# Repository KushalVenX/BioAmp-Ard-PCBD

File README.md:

# Repository Overview

This repository contains a PCB design for the "BioAmp-EXG-Pill" from Upside Down Labs, presented as an open-source hardware project. The design has been adapted and routed on an Arduino template.

## Description

The repository features a PCB design that is a routed adaptation of the BioAmp-EXG-Pill PCB. Although this design utilizes an Arduino template and does not exactly replicate the original design, it serves as a valuable educational resource.

## Purpose:

The repository is intended for educational purposes and learning. It offers an opportunity to:

-**Explore PCB Design**: Understand and study the layout and routing of a real-world PCB.

-**Experiment**: Modify the design for personal projects or educational exercises.

-**Teach**: Use this routed version as a teaching tool for PCB design concepts.

## Original Schematic Credits:

**UPSIDE DOWN LABS**

website: https://upsidedownlabs.tech/

Store: https://store.upsidedownlabs.tech/

github: https://github.com/upsidedownlabs

## Arduino Template credits:

The Arduino template used in this design is based on the Arduino UNO board design by Arduino.cc.

## License:

For details about the licensing of the original design of BioAmp-EXG-Pill, please refer to the Upside Down Labs GitHub repository.

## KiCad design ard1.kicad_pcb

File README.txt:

# Repository Overview
-------------------

This repository contains a PCB design for the "BioAmp-EXG-Pill" from Upside Down Labs, presented as an open-source hardware project. The design has been adapted and routed on an Arduino template.

## Description
------------

The repository features a PCB design that is a routed adaptation of the BioAmp-EXG-Pill PCB. Although this design utilizes an Arduino template and does not exactly replicate the original design, it serves as a valuable educational resource.

## Purpose:
---------
The repository is intended for educational purposes and learning. It offers an opportunity to:

-Explore PCB Design: Understand and study the layout and routing of a real-world PCB.
-Experiment: Modify the design for personal projects or educational exercises.
-Teach: Use this routed version as a teaching tool for PCB design concepts.

## Original Schematic Credits:
---------------------------
website: https://upsidedownlabs.tech/
Store: https://store.upsidedownlabs.tech/
github: https://github.com/upsidedownlabs

## Arduino Template credits:
-------------------------

The Arduino template used in this design is based on the Arduino UNO board design by Arduino.cc.

## License:
--------
For details about the licensing of the original design of BioAmp-EXG-Pill, please refer to the Upside Down Labs GitHub repository.

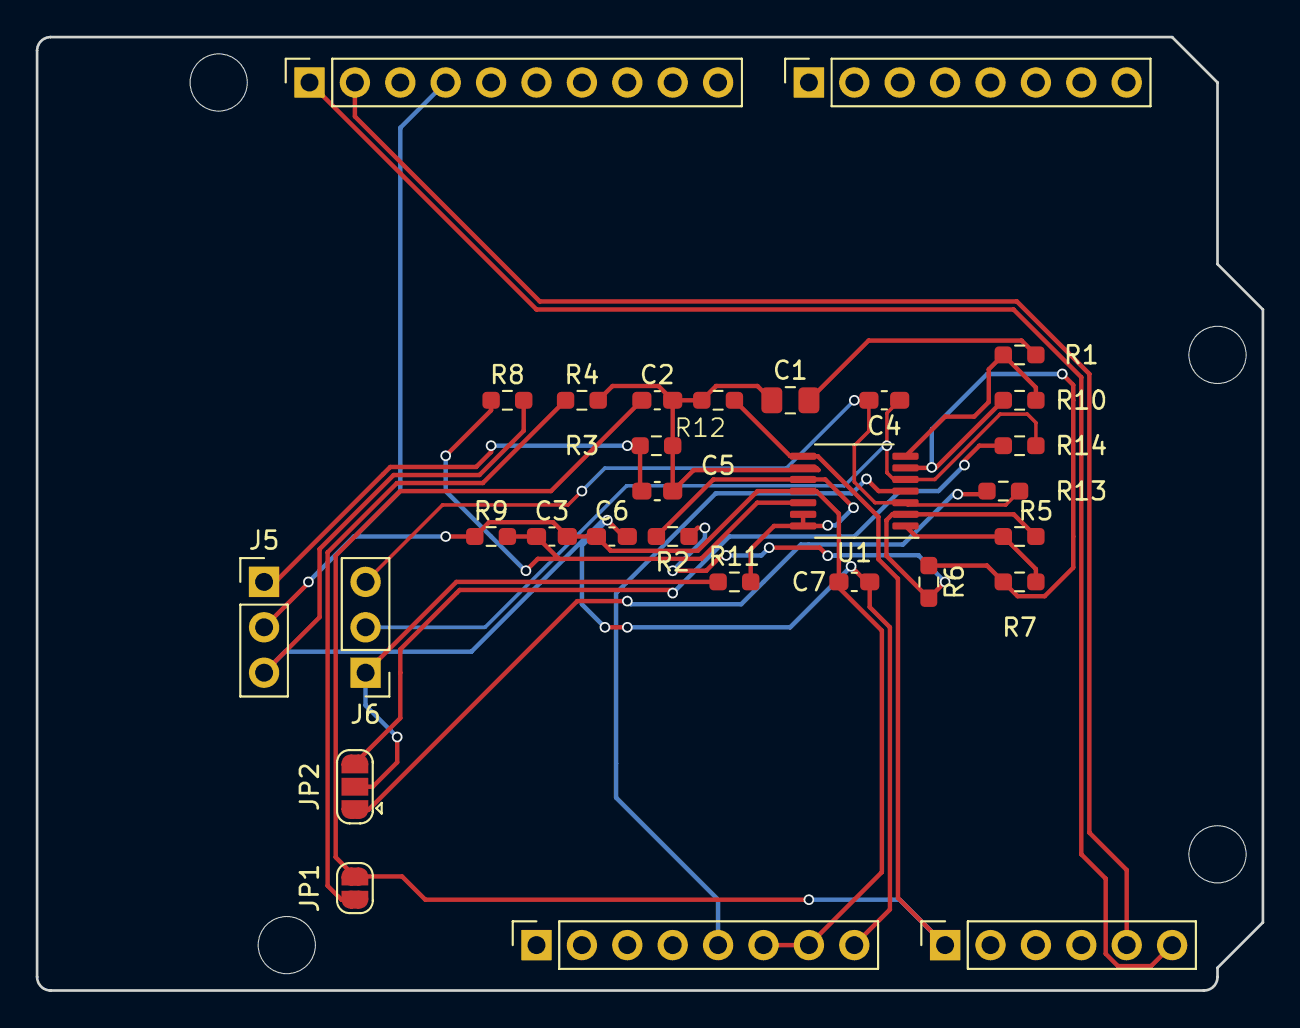
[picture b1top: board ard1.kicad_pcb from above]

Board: 2 copper layers, 68.6 x 53.3 mm, 34 parts (0 on the bottom side), 21 nets.

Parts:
C1: 47uF; C_0805_2012Metric_Pad1.18x1.45mm_HandSolder
C2, C4: 1nF; C_0603_1608Metric_Pad1.08x0.95mm_HandSolder
C3, C7: 10uF; C_0603_1608Metric_Pad1.08x0.95mm_HandSolder
C5: BPFC_C; C_0603_1608Metric_Pad1.08x0.95mm_HandSolder
C6: 100nF; C_0603_1608Metric_Pad1.08x0.95mm_HandSolder
J1: Power; PinSocket_1x08_P2.54mm_Vertical
J2: Analog; PinSocket_1x06_P2.54mm_Vertical
J3: Digital/PWM; PinSocket_1x10_P2.54mm_Vertical
J4: Digital/PWM; PinSocket_1x08_P2.54mm_Vertical
J5: BioAmp Output; PinHeader_1x03_P2.54mm_Vertical
J6: BioAmp Input; PinHeader_1x03_P2.54mm_Vertical
JP1: SolderJumper_2_Open; SolderJumper-2_P1.3mm_Open_RoundedPad1.0x1.5mm
JP2: SolderJumper_3_Open; SolderJumper-3_P1.3mm_Open_RoundedPad1.0x1.5mm
MH1, MH2, MH3, MH4: MountingHole_3.2mm
R1: 1K; R_0603_1608Metric_Pad0.98x0.95mm_HandSolder
R2, R4, R10: 220K; R_0603_1608Metric_Pad0.98x0.95mm_HandSolder
R3, R8, R9, R13, R14: 1M; R_0603_1608Metric_Pad0.98x0.95mm_HandSolder
R5, R7: 22K; R_0603_1608Metric_Pad0.98x0.95mm_HandSolder
R6: RG; R_0603_1608Metric_Pad0.98x0.95mm_HandSolder
R11: 0R; R_0603_1608Metric_Pad0.98x0.95mm_HandSolder
R12: BPFC_R; R_0603_1608Metric_Pad0.98x0.95mm_HandSolder
U1: Amp; TSSOP-14_4.4x5mm_P0.65mm

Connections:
+5V: J1.5, U1.4 (V+)
/A0: C2.1, J2.1, JP1.2 (B), R3.1, U1.8
/SCL/A5: J2.6, J3.1
/SDA/A4: J2.5, J3.2
DRL: J6.1, JP2.2 (C), R11.1
GND: C3.2, C6.1, C7.1, J1.6, J1.7, J3.4, J5.2, R9.1, U1.11 (V-)
IN+: C4.1, J6.2, R14.1, U1.5 (+)
IN-: C4.2, J6.3, R13.2, U1.3 (+)
unnamed: C1.2, R1.1
unnamed: JP1.1 (A), R4.1
unnamed: JP2.1 (A), R13.1
unnamed: JP2.3 (B), R14.2
unnamed: R5.1, R7.2, U1.1
unnamed: R2.1, R5.2, R6.2, U1.2 (-)
unnamed: R6.1, R7.1, R10.2, U1.6 (-)
unnamed: C3.1, R8.1, R9.2, U1.12 (+)
VCC: C6.2, C7.2, J1.8, J5.3, R8.2
ampRef: R2.2, R11.2, U1.10 (+), U1.13 (-), U1.14
bpfIN: C1.1, C2.2, C5.2, R3.2, R4.2, R12.2, U1.9 (-)
bpfOUT: C5.1, J5.1, R12.1
inaOUT: R1.2, R10.1, U1.7

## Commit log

2024-07-31 Added to github
2024-07-31 Changed README extension text to md
2024-07-31 Updated README added image
2024-07-31 Updated README resize image
2024-07-31 Updated README resize images
2024-07-31 Updated README resize images 2
2024-07-31 Updated README resize images 3
2024-07-31 Updated README and modify text
